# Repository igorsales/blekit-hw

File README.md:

This repo contains the BLEKit Hardware design files.

You should open these files with [Eagle CAD Software](http://www.cadsoftusa.com/download-eagle/)

Board and schametic files as under `eagle/projects/blekit`.

Libraries used are in `eagle/lbr`

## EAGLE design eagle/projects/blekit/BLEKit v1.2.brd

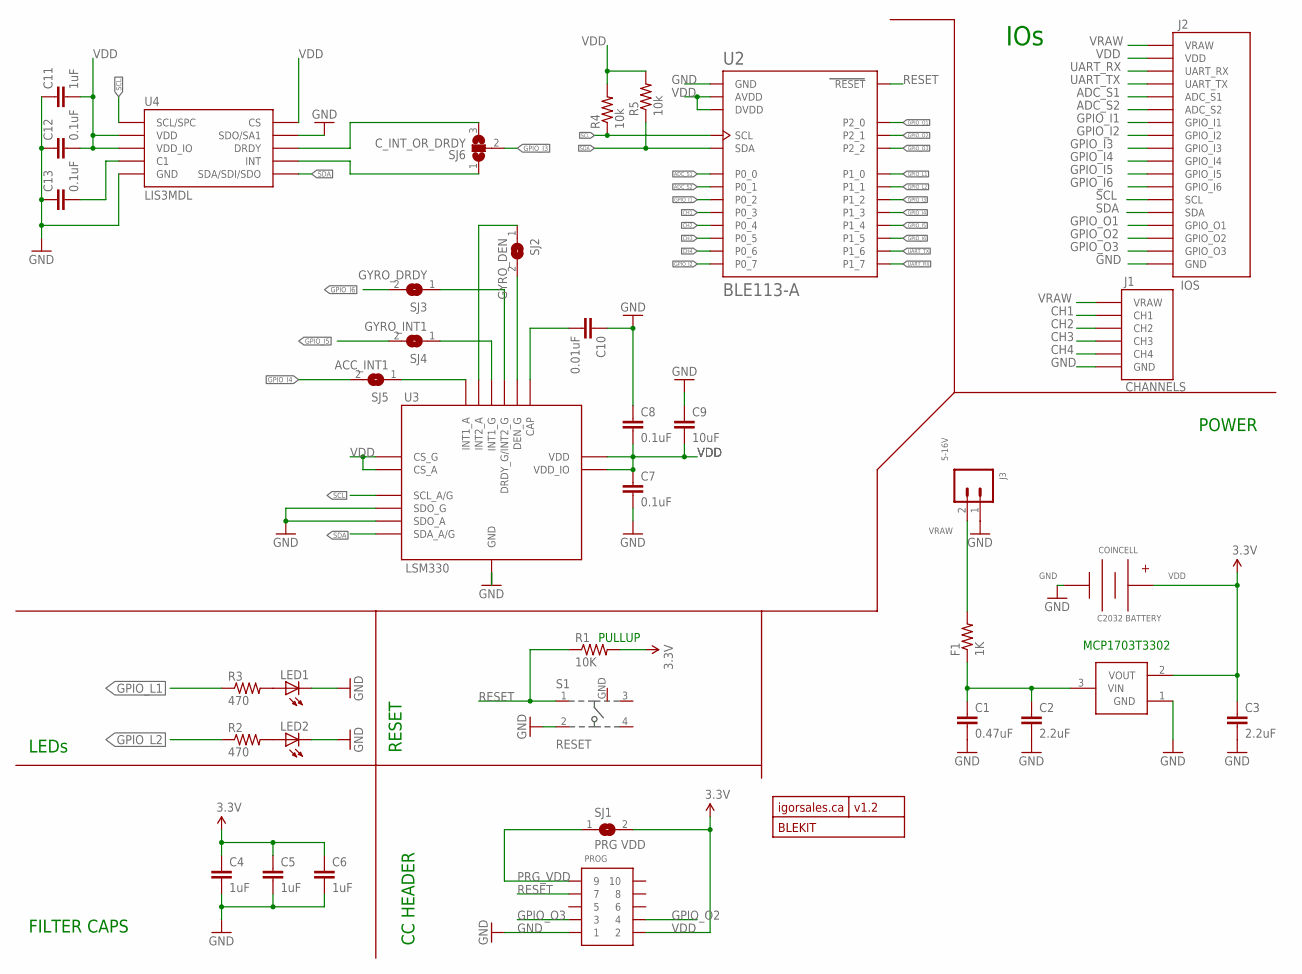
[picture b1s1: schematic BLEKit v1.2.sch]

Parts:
BLEKIT: v1.2; IGORSALES_LOGO
C1: 0.47uF; 0603-CAP; MOUSER# 81-GRM188R60J474KA01
C2, C3: 2.2uF; 0603-CAP; MOUSER# 81-GRM188R61A225KE4J
C4, C5, C6, C11: 1uF; 0603-CAP; MOUSER# 81-GRM188R61C105KA3J
C7, C8, C12, C13: 0.1uF; 0603-CAP; MOUSER# 81-GRM39X104K16
C9: 10uF; 0603-CAP; MOUSER# 963-EMK107BBJ106MA-T
C10: 0.01uF; C0402; VOLTAGE 25V; MOUSER# 81-GRM36X103K25
COINCELL: C2032 BATTERY; BK-912; MPN BK-912; DIGI-KEY# BK-912-ND
F1: 1K; 0805; MOUSER# 810-MMZ2012R102A
J1: CHANNELS; HEADER3X4-2.54MM; MPN TSW-104-07-T-T; DIGI-KEY# TSW-104-07-T-T-ND
J2: IOS; HEADER2X9-254MM; MOUSER# 649-77313-401-18LF
J3: 5-16V; S2B-PH-SM4-TB
LED1: LEDCHIPLED_0805; CHIPLED_0805; MOUSER# 638-1721SYGCS530E2
LED2: LEDCHIPLED_0805; CHIPLED_0805; MOUSER# 638-172BHC-AN1P23T
PROG: CONN_5-2-FTSH-V; FTSH-105-DV; MOUSER# 649-202112100010C4LF; DIGI-KEY# FTSH-105-02-F-DV-ND
R1: 10K; 0603-RES; MOUSER# 603-AF0603FR-0710KL
R2, R3: 470; R0603; MOUSER# 667-ERJ-3EKF4700V
R4, R5: 10k; R0402; VOLTAGE 50V; MOUSER# 603-AF0603FR-0710KL
S1: RESET; 101-IG; MOUSER# 101-IG23K-EV
SJ1: PRG VDD; SJ
SJ2: GYRO_DEN; SJ
SJ3: GYRO_DRDY; SJ
SJ4: GYRO_INT1; SJ
SJ5: ACC_INT1; SJ
SJ6: C_INT_OR_DRDY; SJ_2
U1: MCP1703; SOT-23A; MOUSER# 579-MCP1703T-3302ECB; DIGI-KEY# MCP1703T-3302E/CBCT-ND
U2: BLE113-A; MOUSER# 603-BLE113-A-M256K; DIGI-KEY# 1446-1035-1-ND
U3: LSM330; LGA-24-3.5X3X1MM; MOUSER# 511-LSM330TR
U4: LIS3MDL; VFLGA-2X2X1-12LD; MOUSER# 511-LIS3MDLTR

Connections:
ADC_S1: J2.7 (ADC_S1), U2.P0_0
ADC_S2: J2.16 (ADC_S2), U2.P0_1
CH1: J1.9 (CH1), U2.P0_3
CH2: J1.10 (CH2), U2.P0_4
CH3: J1.11 (CH3), U2.P0_5
CH4: J1.12 (CH4), U2.P0_6
GND: C1.2, C2.2, C3.2, C4.2, C5.2, C6.2, C7.2, C8.1, C9.1, C10.1, C11.1, C12.1, C13.1, COINCELL.BATT- (-), J1.1 (GND), J1.2 (GND), J1.3 (GND), J1.4 (GND), J2.1 (GND), J3.1, LED1.C, LED2.C, PROG.1, S1.2, S1.GND, U1.1 (GND), U2.GND, U2.GND@2 (GND), U2.GND@3 (GND), U2.GND@4 (GND), U2.GND@5 (GND), U2.GND@6 (GND), U2.GND@7 (GND), U2.GND@8 (GND), U2.GND@9 (GND), U2.GND@10 (GND), U3.5 (SDO_G), U3.6 (SDO_A), U3.14 (GND), U3.15 (GND), U3.16 (GND), U3.17 (GND), U3.18 (GND), U3.19 (GND), U3.20 (GND), U4.2 (GND), U4.3 (GND), U4.9 (SDO/SA1), U4.12 (GND)
GPIO_I1: J2.4 (GPIO_I1), U2.P0_2
GPIO_I2: J2.13 (GPIO_I2), U2.P0_7
GPIO_I3: J2.5 (GPIO_I3), SJ6.2, U2.P1_2
GPIO_I4: J2.14 (GPIO_I4), SJ5.2, U2.P1_3
GPIO_I5: J2.6 (GPIO_I5), SJ4.2, U2.P1_4
GPIO_I6: J2.15 (GPIO_I6), SJ3.2, U2.P1_5
GPIO_L1: R3.1, U2.P1_0
GPIO_L2: R2.1, U2.P1_1
GPIO_O1: J2.11 (GPIO_O1), U2.P2_0
GPIO_O2: J2.3 (GPIO_O2), PROG.4, U2.P2_1
GPIO_O3: J2.12 (GPIO_O3), PROG.3, U2.P2_2
unnamed: LED2.A, R2.2
unnamed: SJ2.2, U3.13 (DEN_G)
unnamed: SJ2.1, U3.12 (INT2_A)
unnamed: LED1.A, R3.2
unnamed: C10.2, U3.21 (CAP)
unnamed: C13.2, U4.4 (C1)
unnamed: SJ5.1, U3.11 (INT1_A)
unnamed: SJ3.1, U3.9 (DRDY_G/INT2_G)
unnamed: SJ6.3, U4.8 (DRDY)
unnamed: SJ4.1, U3.10 (INT1_G)
unnamed: SJ6.1, U4.7 (INT)
PRG_VDD: PROG.9, SJ1.1
RESET: PROG.7, R1.1, S1.1, U2.RESET
SCL: J2.9 (SCL), R4.1, U2.SCL, U3.2 (SCL_A/G), U4.1 (SCL/SPC)
SDA: J2.18 (SDA), R5.1, U2.SDA, U3.4 (SDA_A/G), U4.11 (SDA/SDI/SDO)
UART_RX: J2.8 (UART_RX), U2.P1_7
UART_TX: J2.17 (UART_TX), U2.P1_6
VDD: C3.1, C4.1, C5.1, C6.1, C7.1, C8.2, C9.2, C11.2, C12.2, COINCELL.BATT+ (+), COINCELL.BATT+@2 (+), J2.2 (VDD), PROG.2, R1.2, R4.2, R5.2, SJ1.2, U1.2 (VOUT), U2.AVDD, U2.DVDD, U3.1 (VDD_IO), U3.3 (VDD_IO), U3.7 (CS_G), U3.8 (CS_A), U3.22 (VDD), U3.23 (VDD), U3.24 (VDD), U4.5 (VDD), U4.6 (VDD_IO), U4.10 (CS)
VRAW: F1.2, J1.5 (VRAW), J1.6 (VRAW), J1.7 (VRAW), J1.8 (VRAW), J2.10 (VRAW), J3.2
VRAW_FILTERED: C1.1, C2.1, F1.1, U1.3 (VIN)

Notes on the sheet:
MCP1703T3302
CC HEADER
FILTER CAPS
LEDs
RESET
PULLUP
POWER
IOs

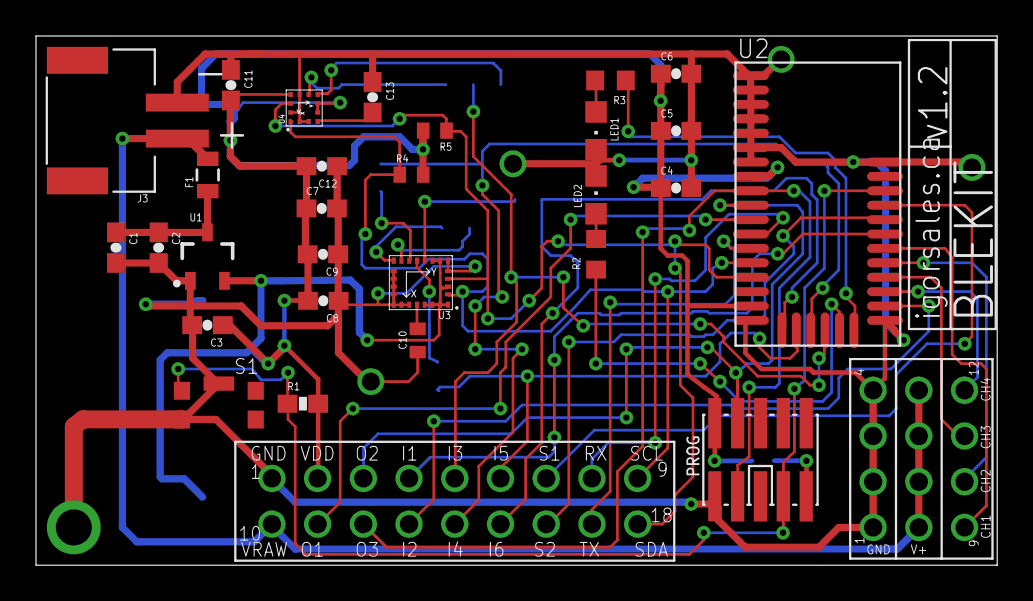
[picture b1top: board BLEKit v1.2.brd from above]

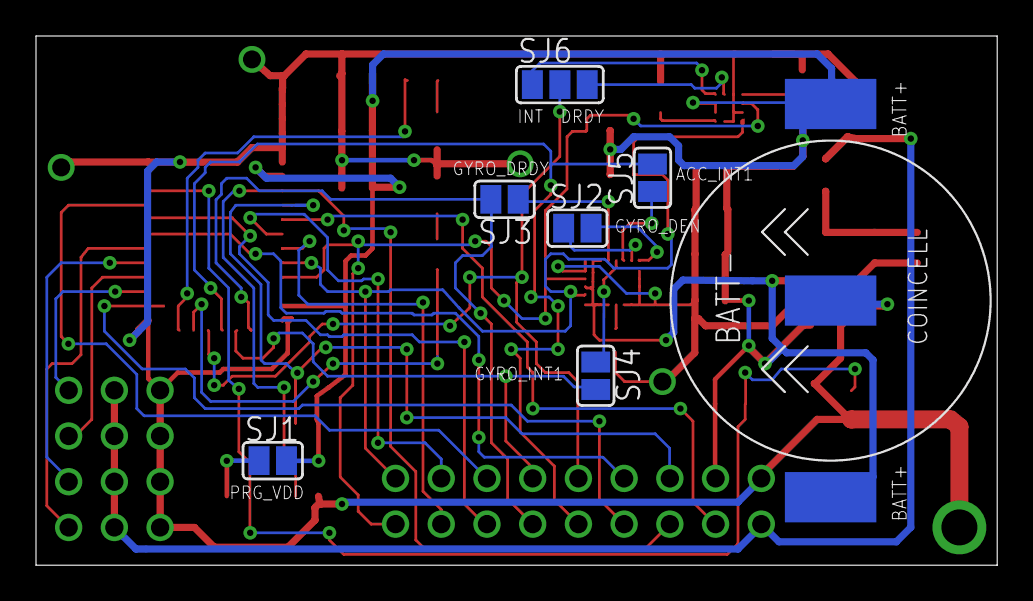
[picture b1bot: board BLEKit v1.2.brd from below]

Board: 2 copper layers, 53.4 x 29.4 mm, 38 parts (6 on the bottom side), 38 nets.

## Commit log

2016-07-07 Initial revision

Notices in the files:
parts and their libraries:
SparkFun: Licensing: CC v3.0 Share-Alike You are welcome to use this library for commercial purposes.
